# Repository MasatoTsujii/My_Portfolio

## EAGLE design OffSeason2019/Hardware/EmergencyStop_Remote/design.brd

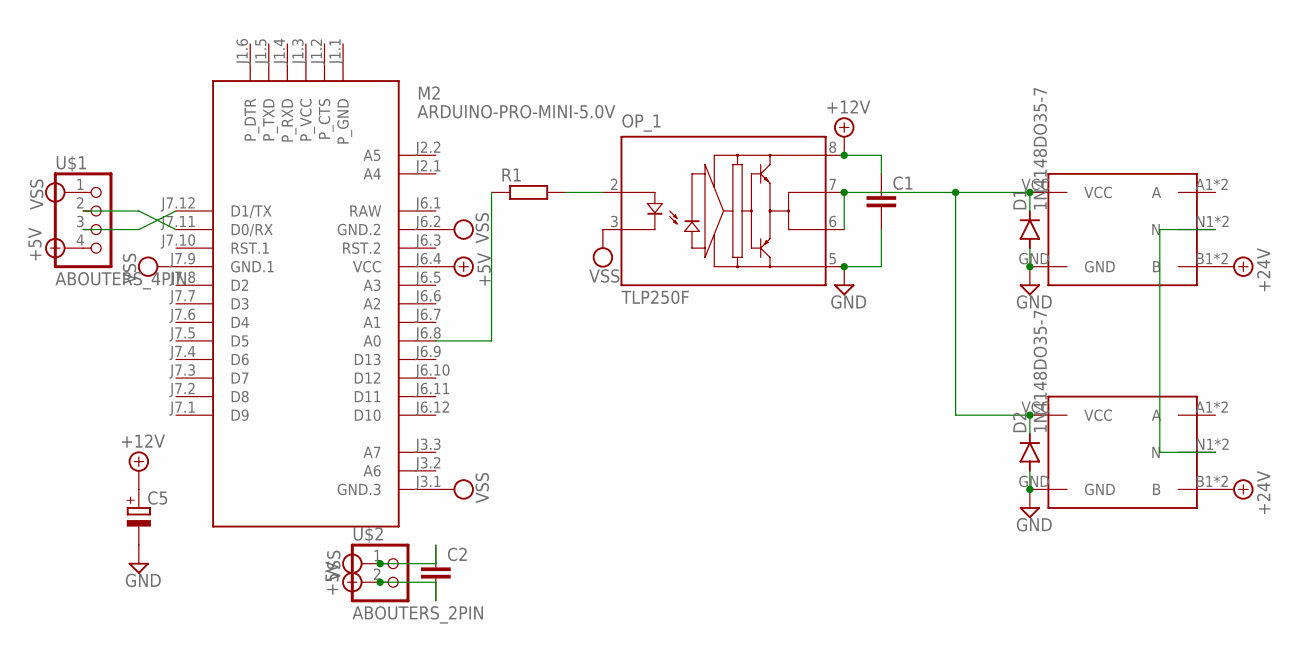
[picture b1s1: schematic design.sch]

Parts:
C1, C2: C-EU025-024X044; C025-024X044
C5: CPOL-EUE5-10.5; E5-10,5
D1, D2: 1N4148DO35-7; DO35-7
HF14FW1, HF14FW2: HF14FW
M2: ARDUINO-PRO-MINI-5.0V; ARDUINO-PRO-MINI
OP_1: TLP250F; DIL08
R1: R-EU_0207/7; 0207/7
U$1: ABOUTERS_4PIN; 22-23-2041
U$2: ABOUTERS_2PIN; 22-23-2021

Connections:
+5V: C2.2, M2.J6.4 (VCC), U$1.4, U$2.2
+12V: C1.1, C5.+, OP_1.8 (VCC)
+24V: HF14FW1.B1 (B), HF14FW1.B2 (B), HF14FW2.B1 (B), HF14FW2.B2 (B)
GND: C1.2, C5.-, D1.A, D2.A, HF14FW1.GND, HF14FW2.GND, OP_1.5 (GND)
unnamed: M2.J7.11 (D0/RX), U$1.2
unnamed: HF14FW1.N1 (N), HF14FW1.N2 (N), HF14FW2.N1 (N), HF14FW2.N2 (N)
unnamed: OP_1.2 (A), R1.2
unnamed: M2.J6.8 (A0), R1.1
unnamed: M2.J7.12 (D1/TX), U$1.3
unnamed: D1.C, D2.C, HF14FW1.VCC, HF14FW2.VCC, OP_1.6 (VO), OP_1.7 (VO')
RAW: M2.J6.1 (RAW)
VSS: C2.1, M2.J3.1 (GND.3), M2.J6.2 (GND.2), M2.J7.9 (GND.1), OP_1.3 (K), U$1.1, U$2.1

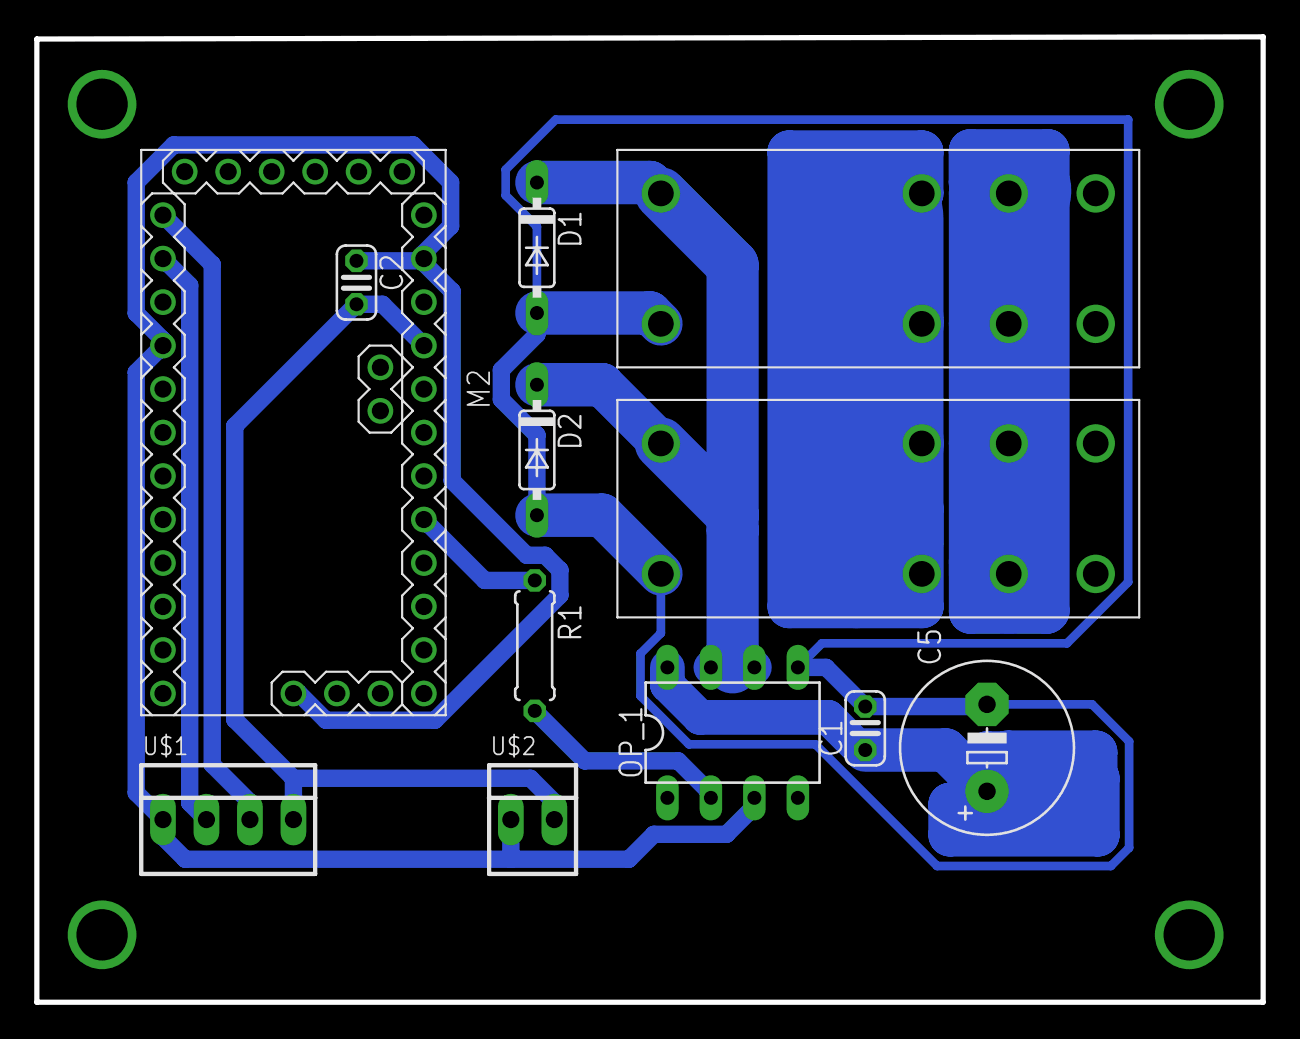
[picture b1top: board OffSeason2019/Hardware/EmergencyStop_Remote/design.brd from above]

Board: 2 copper layers, 71.6 x 56.4 mm, 12 parts (0 on the bottom side), 11 nets.

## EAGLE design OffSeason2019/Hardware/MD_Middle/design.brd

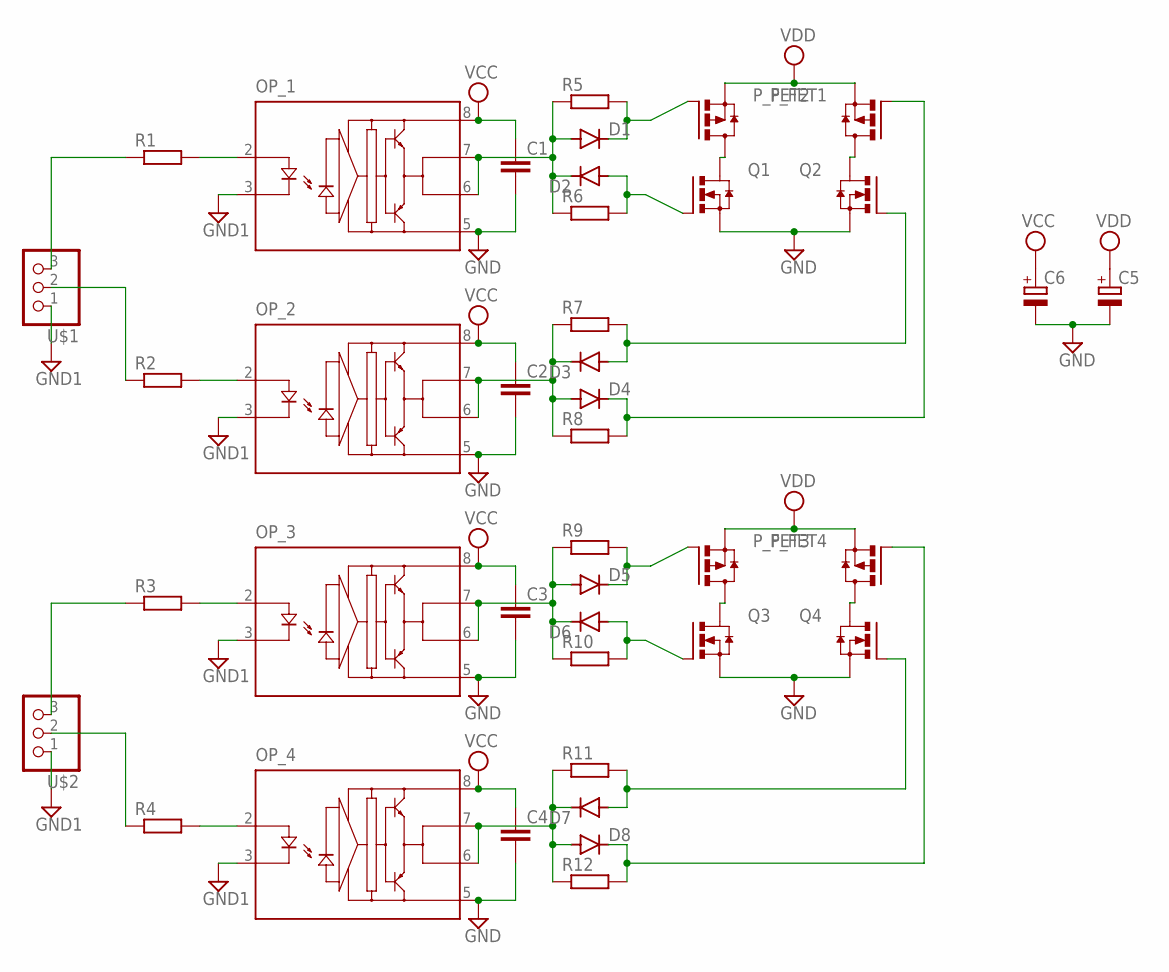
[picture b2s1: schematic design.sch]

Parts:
C1, C2, C3, C4: C-EU025-024X044; C025-024X044
C5: CPOL-EUE5-13; E5-13
C6: CPOL-EUE2.5-7; E2,5-7
D1, D2, D3, D4, D5, D6, D7, D8: 1N4148DO35-7; DO35-7
OP_1, OP_2, OP_3, OP_4: TLP250F; DIL08
P_FET1, P_FET2, P_FET3, P_FET4: P_D2PAK; D2PACK
Q1, Q2, Q3, Q4: IRF3704S; D2PACK
R1, R2, R3, R4, R5, R6, R7, R8, R9, R10, R11, R12: R-EU_0207/7; 0207/7
U$1, U$2: ABOUTERS_3PIN; 22-23-2031

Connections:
GND: C1.2, C2.2, C3.2, C4.2, C5.-, C6.-, OP_1.5 (GND), OP_2.5 (GND), OP_3.5 (GND), OP_4.5 (GND), Q1.3 (S), Q2.3 (S), Q3.3 (S), Q4.3 (S)
GND1: OP_1.3 (K), OP_2.3 (K), OP_3.3 (K), OP_4.3 (K), U$1.1, U$2.1
unnamed: R1.1, U$1.3
unnamed: OP_1.2 (A), R1.2
unnamed: R2.1, U$1.2
unnamed: OP_2.2 (A), R2.2
unnamed: D1.A, D2.C, OP_1.6 (VO), OP_1.7 (VO'), R5.1, R6.1
unnamed: D3.C, D4.A, OP_2.6 (VO), OP_2.7 (VO'), R7.1, R8.1
unnamed: R3.1, U$2.3
unnamed: OP_3.2 (A), R3.2
unnamed: R4.1, U$2.2
unnamed: OP_4.2 (A), R4.2
unnamed: D5.A, D6.C, OP_3.6 (VO), OP_3.7 (VO'), R9.1, R10.1
unnamed: D7.C, D8.A, OP_4.6 (VO), OP_4.7 (VO'), R11.1, R12.1
unnamed: P_FET2.2 (D), Q1.2 (D)
unnamed: D1.C, P_FET2.1 (G), R5.2
unnamed: P_FET1.2 (D), Q2.2 (D)
unnamed: D2.A, Q1.1 (G), R6.2
unnamed: P_FET3.2 (D), Q3.2 (D)
unnamed: D3.A, Q2.1 (G), R7.2
unnamed: D5.C, P_FET3.1 (G), R9.2
unnamed: D4.C, P_FET1.1 (G), R8.2
unnamed: P_FET4.2 (D), Q4.2 (D)
unnamed: D6.A, Q3.1 (G), R10.2
unnamed: D8.C, P_FET4.1 (G), R12.2
unnamed: D7.A, Q4.1 (G), R11.2
VCC: C1.1, C2.1, C3.1, C4.1, C6.+, OP_1.8 (VCC), OP_2.8 (VCC), OP_3.8 (VCC), OP_4.8 (VCC)
VDD: C5.+, P_FET1.3 (S), P_FET2.3 (S), P_FET3.3 (S), P_FET4.3 (S)

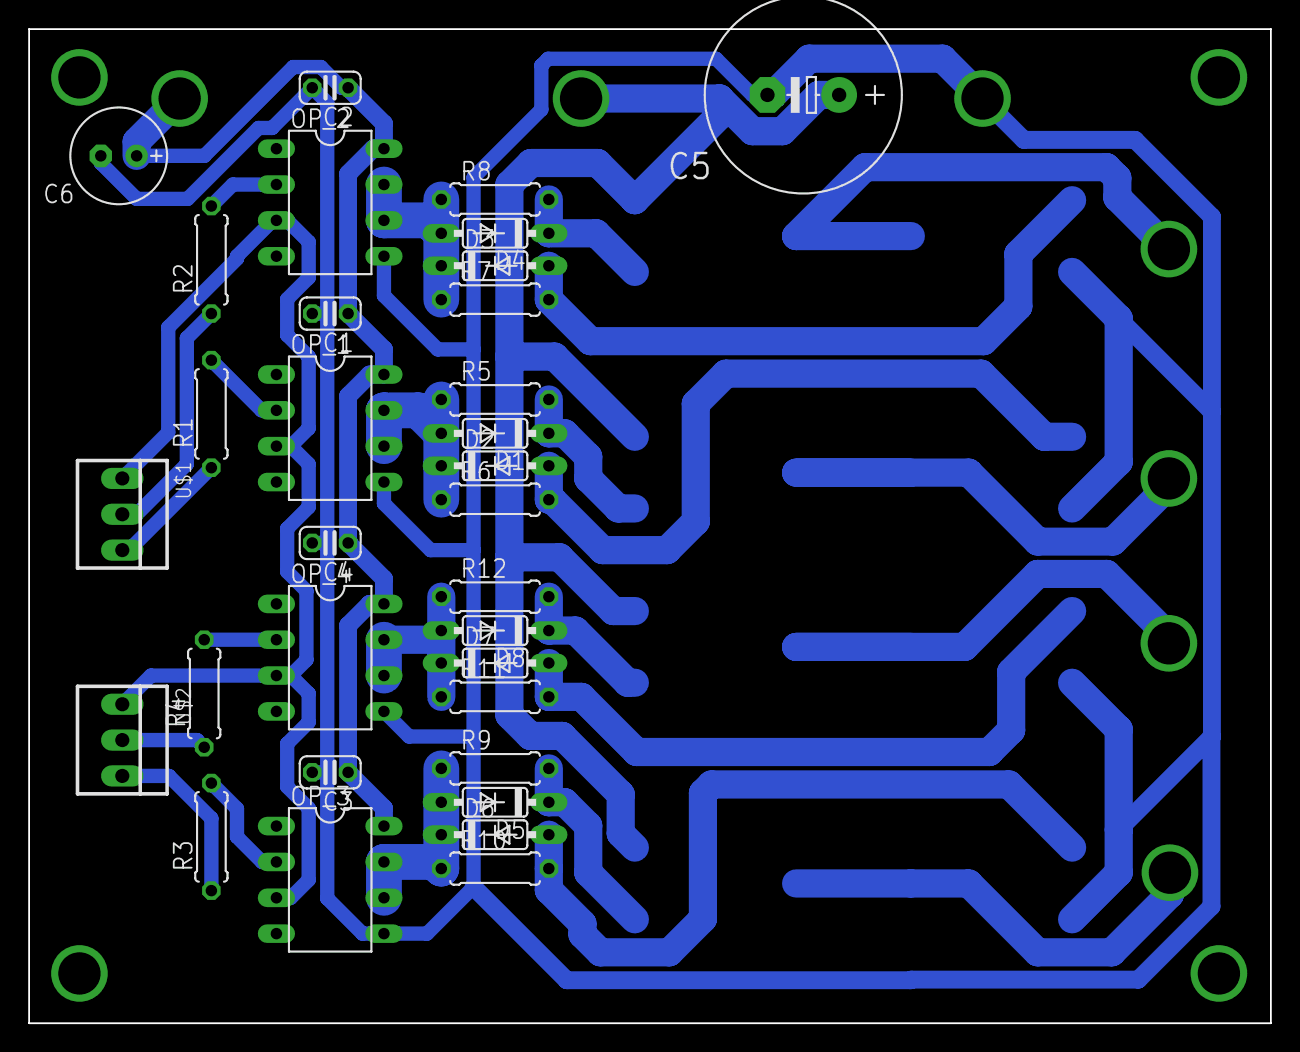
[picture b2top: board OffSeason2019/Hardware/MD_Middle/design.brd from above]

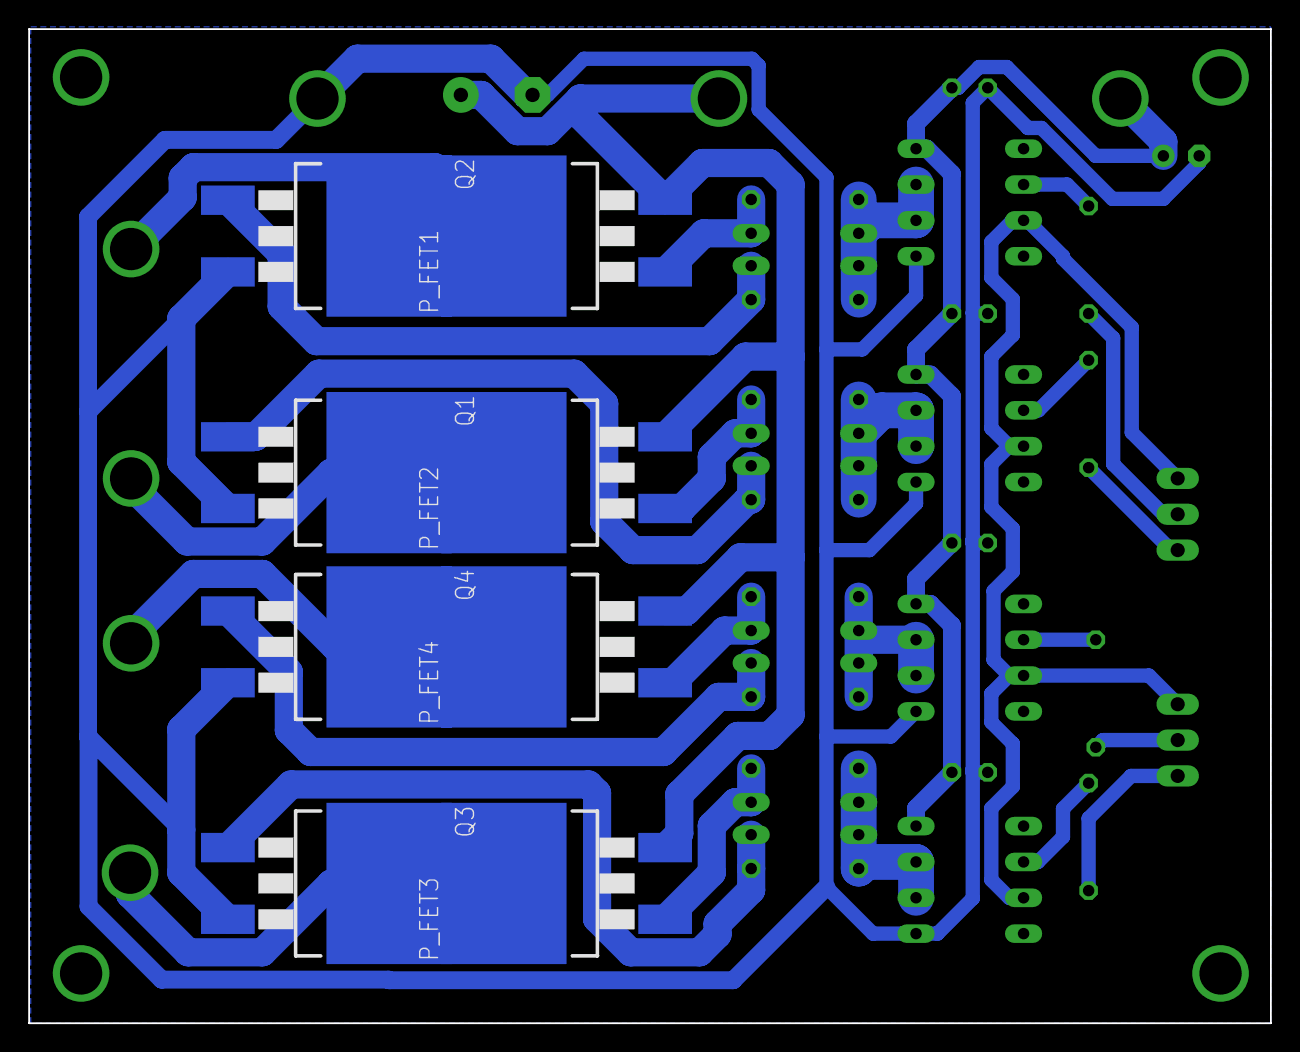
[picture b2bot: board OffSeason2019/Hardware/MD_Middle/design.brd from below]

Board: 2 copper layers, 88.0 x 70.5 mm, 40 parts (8 on the bottom side), 28 nets.

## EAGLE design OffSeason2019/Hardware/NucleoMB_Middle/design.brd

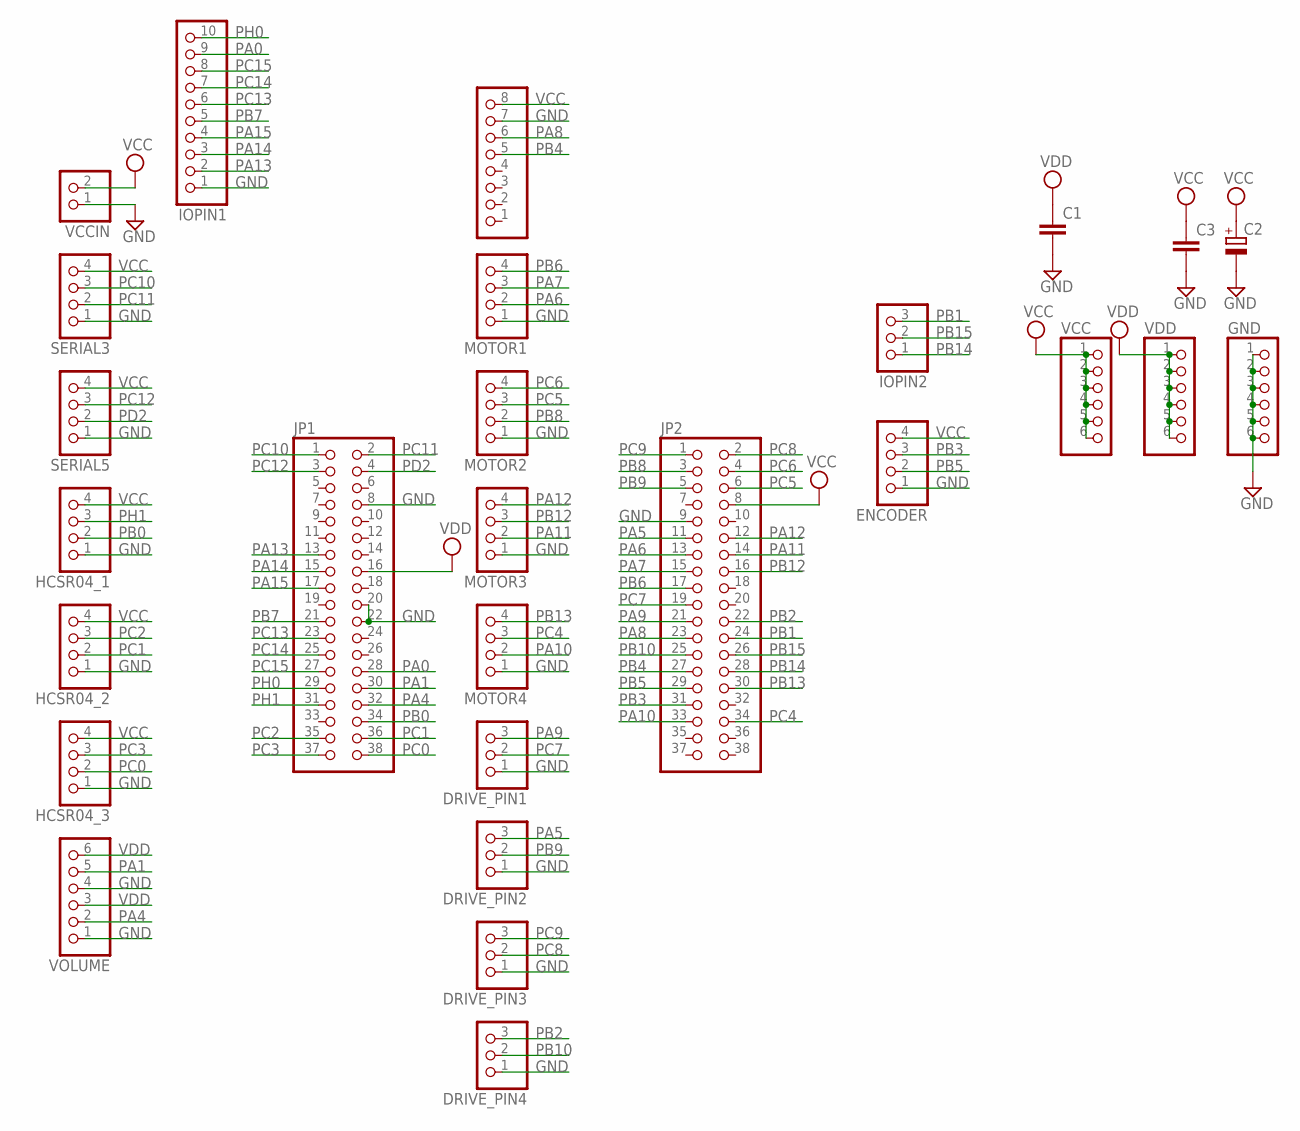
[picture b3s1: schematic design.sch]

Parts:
C1, C3: C-EU025-024X044; C025-024X044
C2: CPOL-EUE2.5-7; E2,5-7
DRIVE_PIN1, DRIVE_PIN2, DRIVE_PIN3, DRIVE_PIN4: ABOUTERS_3PIN; 22-23-2031
ENCODER: ABOUTERS_4PIN; 22-23-2041
GND: ABOUTERS_6PIN; 22-23-2061
HCSR04_1, HCSR04_2, HCSR04_3: ABOUTERS_4PIN; 22-23-2041
IOPIN1: ABOUTERS_10PIN; 22-23-2101
IOPIN2: ABOUTERS_3PIN; 22-23-2031
JP1, JP2: PINHD-2X19; 2X19
JP3: PINHD-1X8; 1X08
MOTOR1, MOTOR2, MOTOR3, MOTOR4: ABOUTERS_4PIN; 22-23-2041
SERIAL3, SERIAL5: ABOUTERS_4PIN; 22-23-2041
VCC: ABOUTERS_6PIN; 22-23-2061
VCCIN: ABOUTERS_2PIN; 22-23-2021
VDD: ABOUTERS_6PIN; 22-23-2061
VOLUME: ABOUTERS_6PIN; 22-23-2061

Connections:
GND: C1.2, C2.-, C3.2, DRIVE_PIN1.1, DRIVE_PIN2.1, DRIVE_PIN3.1, DRIVE_PIN4.1, ENCODER.1, GND.1, GND.2, GND.3, GND.4, GND.5, GND.6, HCSR04_1.1, HCSR04_2.1, HCSR04_3.1, IOPIN1.1, JP1.8, JP1.20, JP1.22, JP2.9, JP3.7, MOTOR1.1, MOTOR2.1, MOTOR3.1, MOTOR4.1, SERIAL3.1, SERIAL5.1, VCCIN.1, VOLUME.1, VOLUME.4
PA0: IOPIN1.9, JP1.28
PA1: JP1.30, VOLUME.5
PA4: JP1.32, VOLUME.2
PA5: DRIVE_PIN2.3, JP2.11
PA6: JP2.13, MOTOR1.2
PA7: JP2.15, MOTOR1.3
PA8: JP2.23, JP3.6
PA9: DRIVE_PIN1.3, JP2.21
PA10: JP2.33, MOTOR4.2
PA11: JP2.14, MOTOR3.2
PA12: JP2.12, MOTOR3.4
PA13: IOPIN1.2, JP1.13
PA14: IOPIN1.3, JP1.15
PA15: IOPIN1.4, JP1.17
PB0: HCSR04_1.2, JP1.34
PB1: IOPIN2.3, JP2.24
PB2: DRIVE_PIN4.3, JP2.22
PB3: ENCODER.3, JP2.31
PB4: JP2.27, JP3.5
PB5: ENCODER.2, JP2.29
PB6: JP2.17, MOTOR1.4
PB7: IOPIN1.5, JP1.21
PB8: JP2.3, MOTOR2.2
PB9: DRIVE_PIN2.2, JP2.5
PB10: DRIVE_PIN4.2, JP2.25
PB12: JP2.16, MOTOR3.3
PB13: JP2.30, MOTOR4.4
PB14: IOPIN2.1, JP2.28
PB15: IOPIN2.2, JP2.26
PC0: HCSR04_3.2, JP1.38
PC1: HCSR04_2.2, JP1.36
PC2: HCSR04_2.3, JP1.35
PC3: HCSR04_3.3, JP1.37
PC4: JP2.34, MOTOR4.3
PC5: JP2.6, MOTOR2.3
PC6: JP2.4, MOTOR2.4
PC7: DRIVE_PIN1.2, JP2.19
PC8: DRIVE_PIN3.2, JP2.2
PC9: DRIVE_PIN3.3, JP2.1
PC10: JP1.1, SERIAL3.3
PC11: JP1.2, SERIAL3.2
PC12: JP1.3, SERIAL5.3
PC13: IOPIN1.6, JP1.23
PC14: IOPIN1.7, JP1.25
PC15: IOPIN1.8, JP1.27
PD2: JP1.4, SERIAL5.2
PH0: IOPIN1.10, JP1.29
PH1: HCSR04_1.3, JP1.31
VCC: C2.+, C3.1, ENCODER.4, HCSR04_1.4, HCSR04_2.4, HCSR04_3.4, JP2.8, JP3.8, SERIAL3.4, SERIAL5.4, VCC.1, VCC.2, VCC.3, VCC.4, VCC.5, VCC.6, VCCIN.2
VDD: C1.1, JP1.16, VDD.1, VDD.2, VDD.3, VDD.4, VDD.5, VDD.6, VOLUME.3, VOLUME.6

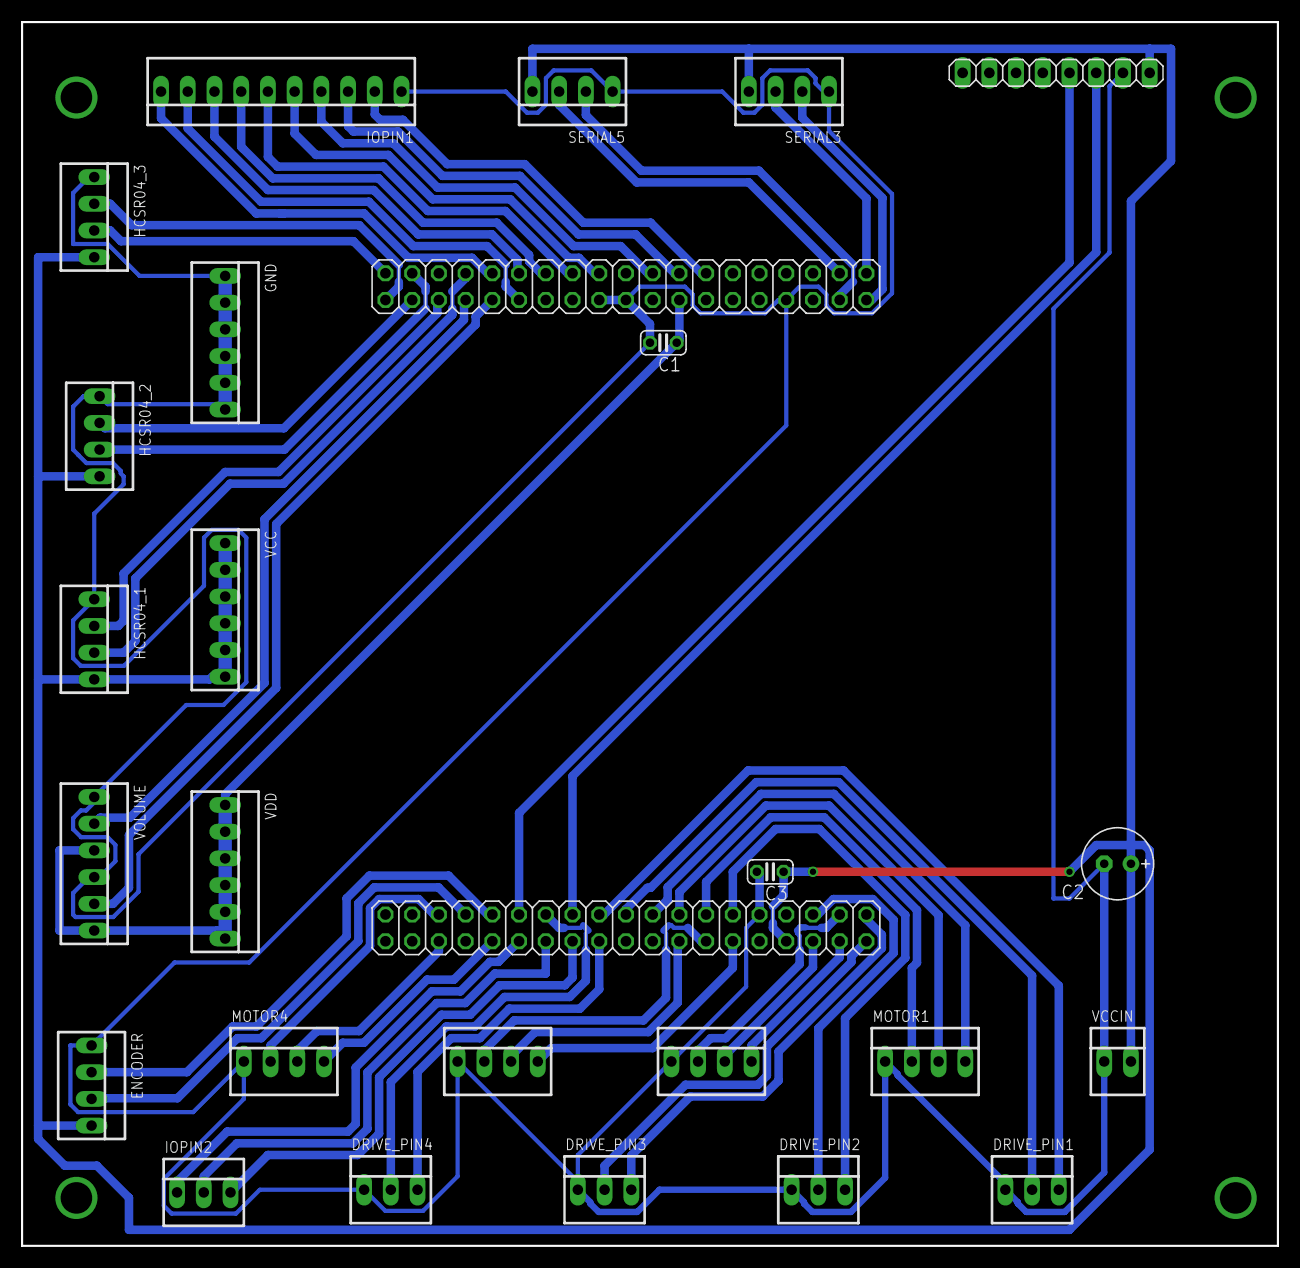
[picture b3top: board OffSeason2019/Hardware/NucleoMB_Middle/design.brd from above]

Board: 2 copper layers, 119.4 x 116.3 mm, 27 parts (0 on the bottom side), 51 nets.

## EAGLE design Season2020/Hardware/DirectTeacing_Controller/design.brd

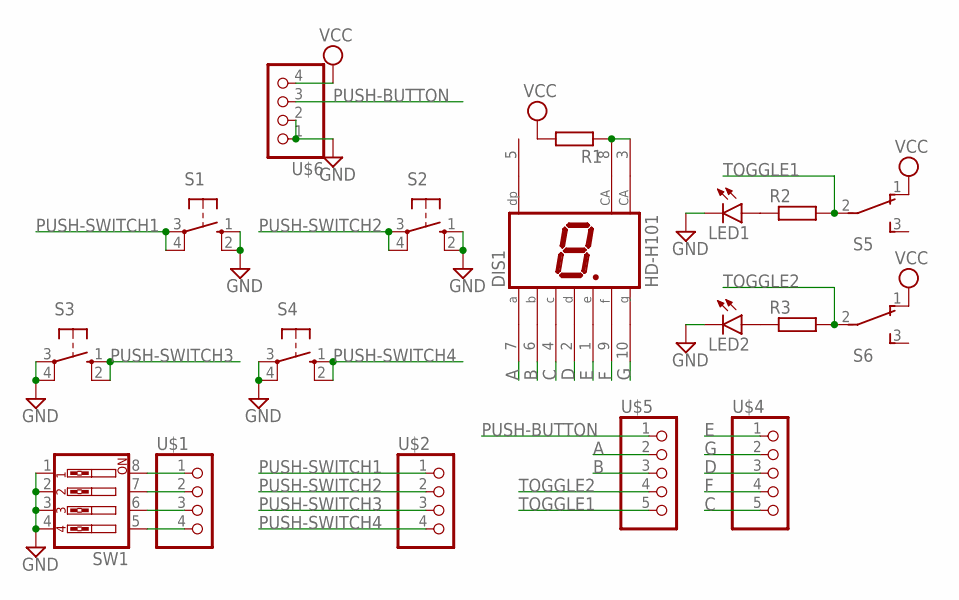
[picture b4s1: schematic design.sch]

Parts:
DIS1: HD-H101; HDSP-M
LED1, LED2: LED5MM
R1, R2, R3: R-EU_0207/10; 0207/10
S1, S2, S3, S4: 10-XX; B3F-10XX
S5, S6: TL36PO; TL3XPO
SW1: SW_DIP-4; EDG-04
U$1, U$2, U$6: ABOUTERS_4PIN; 22-23-2041
U$4, U$5: ABOUTERS_5PIN; 22-23-2051

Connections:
A: DIS1.7 (A), U$5.2
B: DIS1.6 (B), U$5.3
C: DIS1.4 (C), U$4.5
D: DIS1.2 (D), U$4.3
E: DIS1.1 (E), U$4.1
F: DIS1.9 (F), U$4.4
G: DIS1.10 (G), U$4.2
GND: LED1.K (C), LED2.K (C), S1.1 (S), S1.2 (S1), S2.1 (S), S2.2 (S1), S3.3, S3.4 (P1), S4.3, S4.4 (P1), SW1.1, SW1.2, SW1.3, SW1.4, U$6.1, U$6.2
unnamed: DIS1.3 (CA), DIS1.8 (CA), R1.1
unnamed: SW1.8, U$1.1
unnamed: SW1.7, U$1.2
unnamed: SW1.6, U$1.3
unnamed: SW1.5, U$1.4
unnamed: LED1.A, R2.1
unnamed: LED2.A, R3.1
PUSH-BUTTON: U$5.1, U$6.3
PUSH-SWITCH1: S1.3, S1.4 (P1), U$2.1
PUSH-SWITCH2: S2.3, S2.4 (P1), U$2.2
PUSH-SWITCH3: S3.1 (S), S3.2 (S1), U$2.3
PUSH-SWITCH4: S4.1 (S), S4.2 (S1), U$2.4
TOGGLE1: R2.2, S5.2, U$5.5
TOGGLE2: R3.2, S6.2, U$5.4
VCC: R1.2, S5.1 (O), S6.1 (O), U$6.4

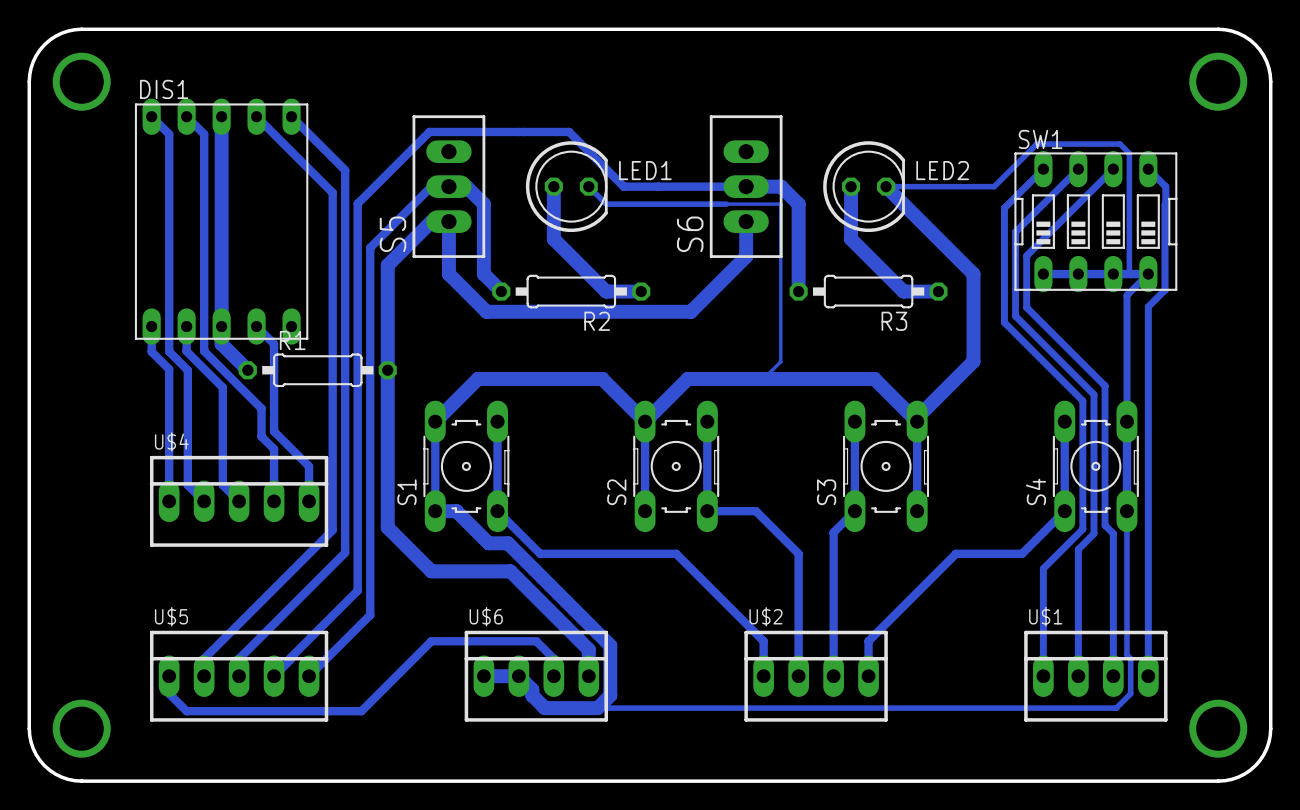
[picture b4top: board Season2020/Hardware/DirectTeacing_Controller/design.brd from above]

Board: 2 copper layers, 90.2 x 54.6 mm, 18 parts (0 on the bottom side), 23 nets.

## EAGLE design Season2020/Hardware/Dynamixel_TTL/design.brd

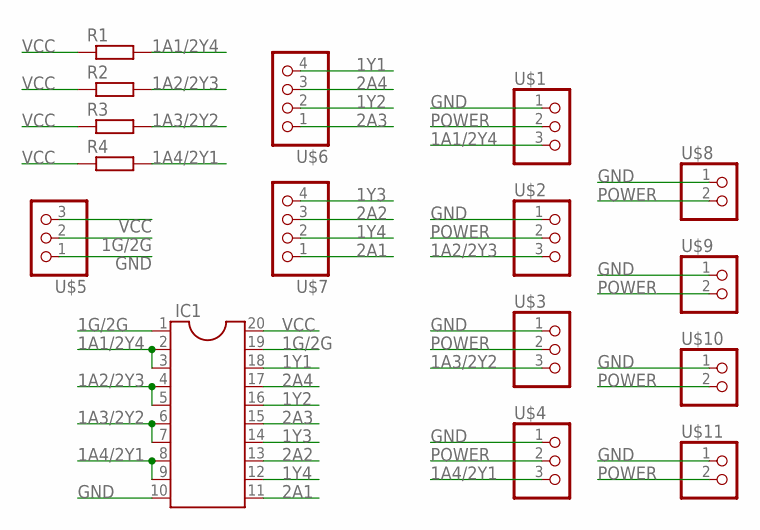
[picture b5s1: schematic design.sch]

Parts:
IC1: DIL20
R1, R2, R3, R4: R-EU_0207/7; 0207/7
U$1, U$2, U$3, U$4, U$5: ABOUTERS_3PIN; 22-23-2031
U$6, U$7: ABOUTERS_4PIN; 22-23-2041
U$8, U$9, U$10, U$11: ABOUTERS_2PIN; 22-23-2021

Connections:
1A1/2Y4: IC1.2, IC1.3, R1.2, U$1.3
1A2/2Y3: IC1.4, IC1.5, R2.2, U$2.3
1A3/2Y2: IC1.6, IC1.7, R3.2, U$3.3
1A4/2Y1: IC1.8, IC1.9, R4.2, U$4.3
1G/2G: IC1.1, IC1.19, U$5.2
1Y1: IC1.18, U$6.4
1Y2: IC1.16, U$6.2
1Y3: IC1.14, U$7.4
1Y4: IC1.12, U$7.2
2A1: IC1.11, U$7.1
2A2: IC1.13, U$7.3
2A3: IC1.15, U$6.1
2A4: IC1.17, U$6.3
GND: IC1.10, U$1.1, U$2.1, U$3.1, U$4.1, U$5.1, U$8.1, U$9.1, U$10.1, U$11.1
POWER: U$1.2, U$2.2, U$3.2, U$4.2, U$8.2, U$9.2, U$10.2, U$11.2
VCC: IC1.20, R1.1, R2.1, R3.1, R4.1, U$5.3

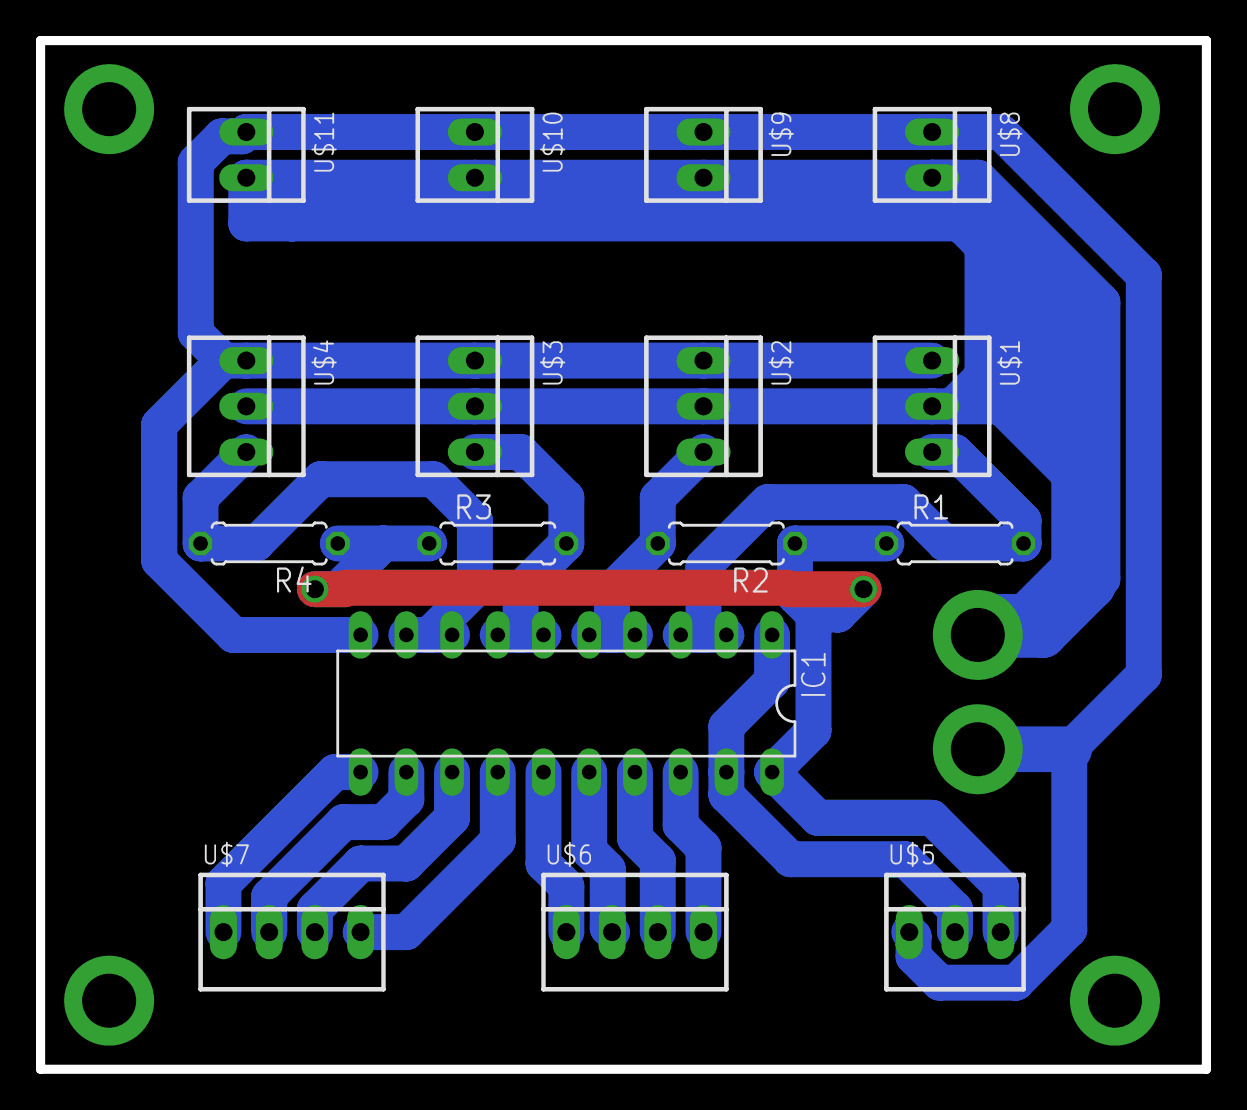
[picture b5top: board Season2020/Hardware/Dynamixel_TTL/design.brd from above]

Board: 2 copper layers, 64.8 x 57.1 mm, 16 parts (0 on the bottom side), 16 nets.

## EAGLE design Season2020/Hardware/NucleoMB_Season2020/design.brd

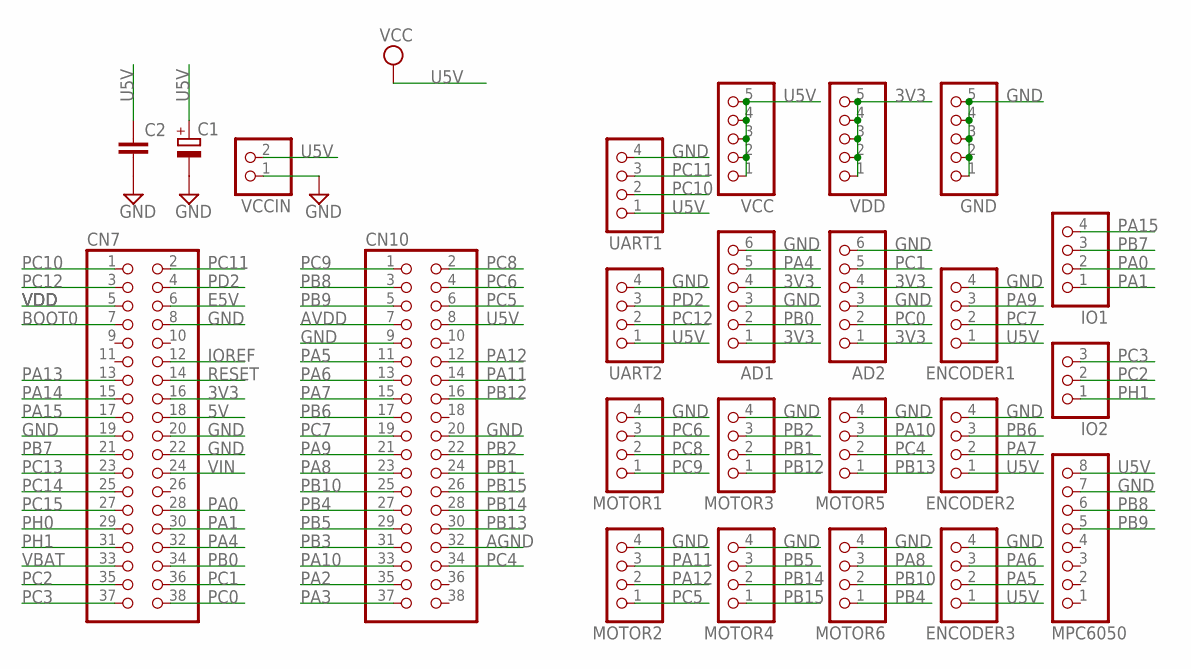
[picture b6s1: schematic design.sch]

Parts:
AD1, AD2: ABOUTERS_6PIN; 22-23-2061
C1: CPOL-EUE2.5-7; E2,5-7
C2: C-EU025-024X044; C025-024X044
CN7, CN10: PINHD-2X19; 2X19
ENCODER1, ENCODER2, ENCODER3: ABOUTERS_4PIN; 22-23-2041
GND: ABOUTERS_5PIN; 22-23-2051
IO1: ABOUTERS_4PIN; 22-23-2041
IO2: ABOUTERS_3PIN; 22-23-2031
MOTOR1, MOTOR2, MOTOR3, MOTOR4, MOTOR5, MOTOR6: ABOUTERS_4PIN; 22-23-2041
MPC6050: ABOUTERS_8PIN; 22-23-2081
UART1, UART2: ABOUTERS_4PIN; 22-23-2041
VCC: ABOUTERS_5PIN; 22-23-2051
VCCIN: ABOUTERS_2PIN; 22-23-2021
VDD: ABOUTERS_5PIN; 22-23-2051

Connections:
3V3: AD1.1, AD1.4, AD2.1, AD2.4, CN7.16, VDD.1, VDD.2, VDD.3, VDD.4, VDD.5
5V: CN7.18
AGND: CN10.32
AVDD: CN10.7
BOOT0: CN7.7
E5V: CN7.6
GND: AD1.3, AD1.6, AD2.3, AD2.6, C1.-, C2.2, CN7.8, CN7.19, CN7.20, CN7.22, CN10.9, CN10.20, ENCODER1.4, ENCODER2.4, ENCODER3.4, GND.1, GND.2, GND.3, GND.4, GND.5, MOTOR1.4, MOTOR2.4, MOTOR3.4, MOTOR4.4, MOTOR5.4, MOTOR6.4, MPC6050.7, UART1.4, UART2.4, VCCIN.1
IOREF: CN7.12
PA0: CN7.28, IO1.2
PA1: CN7.30, IO1.1
PA2: CN10.35
PA3: CN10.37
PA4: AD1.5, CN7.32
PA5: CN10.11, ENCODER3.2
PA6: CN10.13, ENCODER3.3
PA7: CN10.15, ENCODER2.2
PA8: CN10.23, MOTOR6.3
PA9: CN10.21, ENCODER1.3
PA10: CN10.33, MOTOR5.3
PA11: CN10.14, MOTOR2.3
PA12: CN10.12, MOTOR2.2
PA13: CN7.13
PA14: CN7.15
PA15: CN7.17, IO1.4
PB0: AD1.2, CN7.34
PB1: CN10.24, MOTOR3.2
PB2: CN10.22, MOTOR3.3
PB3: CN10.31
PB4: CN10.27, MOTOR6.1
PB5: CN10.29, MOTOR4.3
PB6: CN10.17, ENCODER2.3
PB7: CN7.21, IO1.3
PB8: CN10.3, MPC6050.6
PB9: CN10.5, MPC6050.5
PB10: CN10.25, MOTOR6.2
PB12: CN10.16, MOTOR3.1
PB13: CN10.30, MOTOR5.1
PB14: CN10.28, MOTOR4.2
PB15: CN10.26, MOTOR4.1
PC0: AD2.2, CN7.38
PC1: AD2.5, CN7.36
PC2: CN7.35, IO2.2
PC3: CN7.37, IO2.3
PC4: CN10.34, MOTOR5.2
PC5: CN10.6, MOTOR2.1
PC6: CN10.4, MOTOR1.3
PC7: CN10.19, ENCODER1.2
PC8: CN10.2, MOTOR1.2
PC9: CN10.1, MOTOR1.1
PC10: CN7.1, UART1.2
PC11: CN7.2, UART1.3
PC12: CN7.3, UART2.2
PC13: CN7.23
PC14: CN7.25
PC15: CN7.27
PD2: CN7.4, UART2.3
PH0: CN7.29
PH1: CN7.31, IO2.1
RESET: CN7.14
U5V: C1.+, C2.1, CN10.8, ENCODER1.1, ENCODER2.1, ENCODER3.1, MPC6050.8, UART1.1, UART2.1, VCC.1, VCC.2, VCC.3, VCC.4, VCC.5, VCCIN.2
VBAT: CN7.33
VDD: CN7.5
VIN: CN7.24

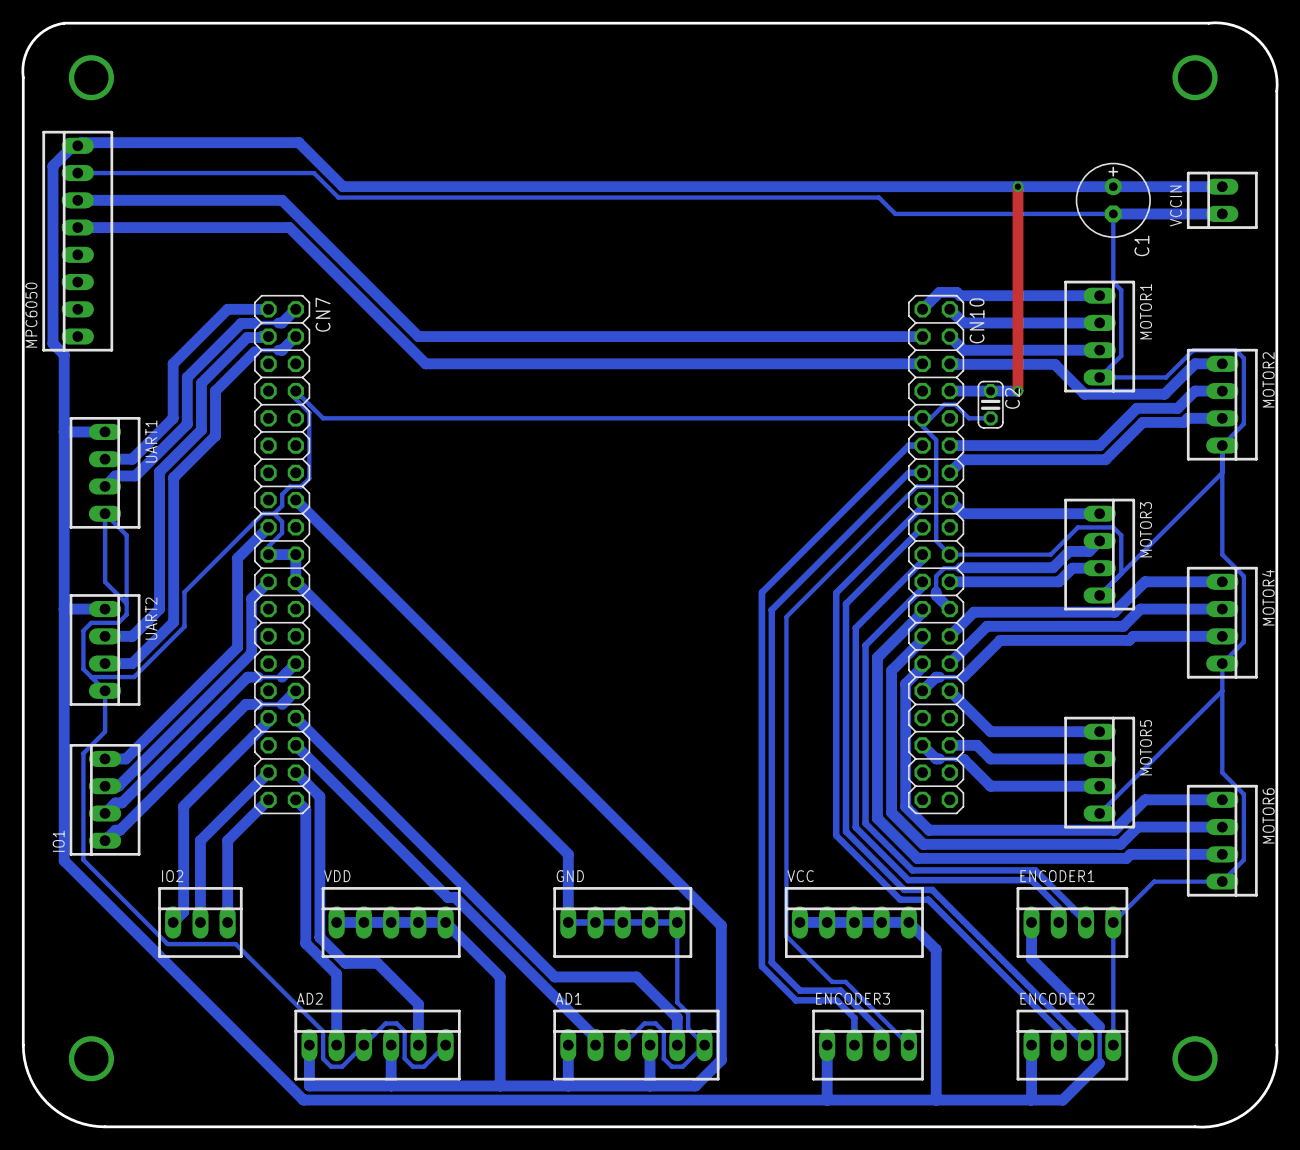
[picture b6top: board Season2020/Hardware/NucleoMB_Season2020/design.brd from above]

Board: 2 copper layers, 116.9 x 102.9 mm, 24 parts (0 on the bottom side), 44 nets.

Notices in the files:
parts and their libraries:
diy-modules: Released under the Creative Commons Attribution 4.0 International License: http://creativecommons.org/licenses/by/4.0
